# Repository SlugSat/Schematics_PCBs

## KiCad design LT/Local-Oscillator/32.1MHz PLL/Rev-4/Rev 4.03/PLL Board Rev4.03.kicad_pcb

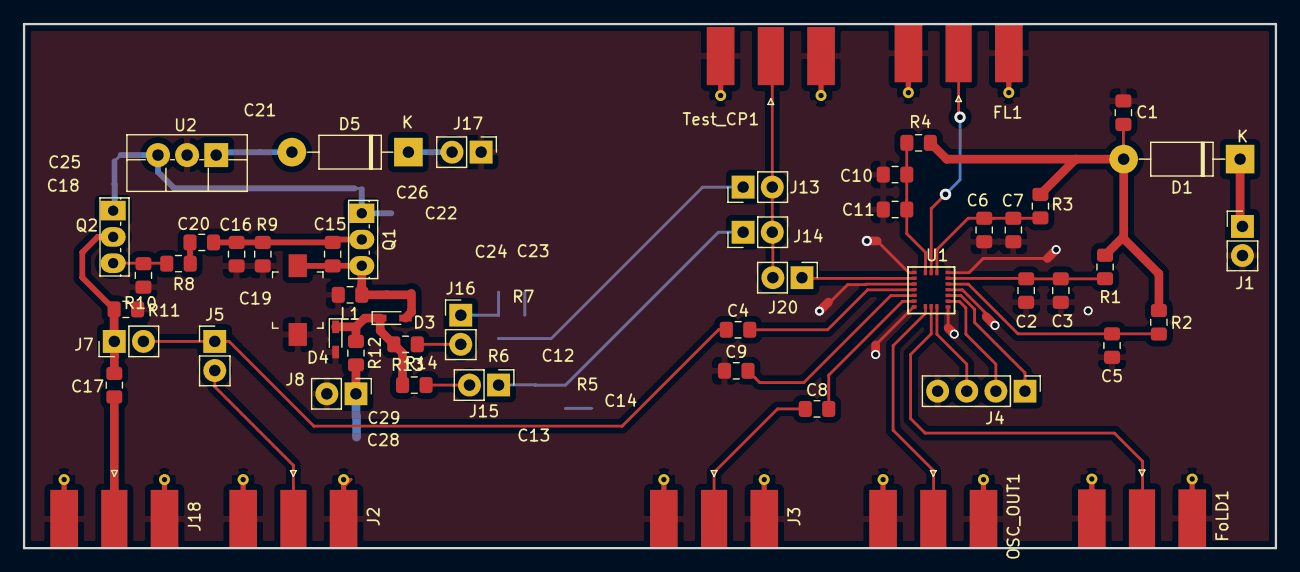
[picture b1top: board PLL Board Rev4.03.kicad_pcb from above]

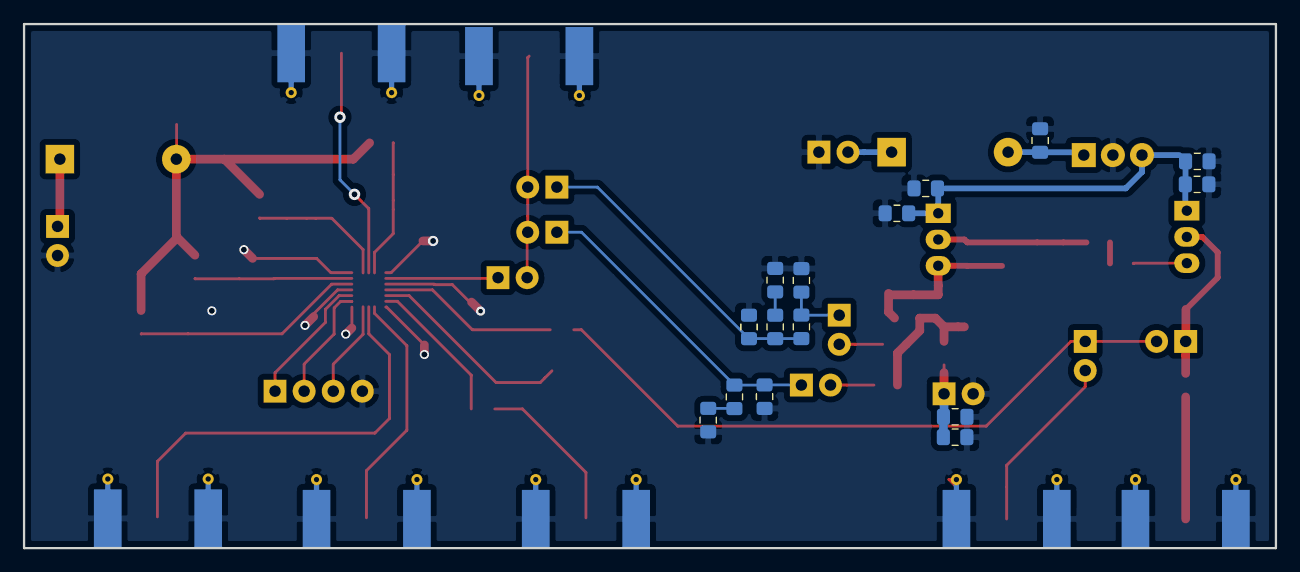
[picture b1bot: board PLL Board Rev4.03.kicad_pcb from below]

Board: 2 copper layers, 109.2 x 45.7 mm, 69 parts (15 on the bottom side), 39 nets.

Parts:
C1, C13, C14: C; C_0805_2012Metric_Pad1.15x1.40mm_HandSolder
C2, C5, C6, C9, C10, C17, C18, C21, C22, C29: 100nF; C_0805_2012Metric_Pad1.15x1.40mm_HandSolder
C3, C7, C11, C25, C26, C28: 100pF; C_0805_2012Metric_Pad1.15x1.40mm_HandSolder
C4, C8: 1000pF; C_0805_2012Metric_Pad1.15x1.40mm_HandSolder
C12: 12nF; C_0805_2012Metric_Pad1.15x1.40mm_HandSolder
C15: 22pF; C_0805_2012Metric_Pad1.15x1.40mm_HandSolder
C16: 47pF; C_0805_2012Metric_Pad1.15x1.40mm_HandSolder
C19: TZB4Z100BA10R00; C_Trimmer_Murata_TZB4-B
C20: 10pF; C_0805_2012Metric_Pad1.15x1.40mm_HandSolder
C23: 80nF; C_0805_2012Metric_Pad1.15x1.40mm_HandSolder
C24: 220nF; C_0805_2012Metric_Pad1.15x1.40mm_HandSolder
D1, D5: DIODE; D_DO-41_SOD81_P10.16mm_Horizontal
D3, D4: ???; D_SC-80_HandSoldering
FL1: Conn_Coaxial; SMA_Molex_73251-1153_EdgeMount_Horizontal
FoLD1: Conn_Coaxial; SMA_Molex_73251-1153_EdgeMount_Horizontal
J1, J5, J7, J8, J13, J14, J15, J16, J17, J20: Conn_01x02_Male; PinHeader_1x02_P2.54mm_Vertical
J2, J3, J18: Conn_Coaxial; SMA_Molex_73251-1153_EdgeMount_Horizontal
J4: Conn_01x04_Male; PinHeader_1x04_P2.54mm_Vertical
L1: 680nH; L_0805_2012Metric_Pad1.15x1.40mm_HandSolder
OSC_OUT1: Conn_Coaxial; SMA_Molex_73251-1153_EdgeMount_Horizontal
Q1, Q2: 2N5486 JFET; TO-251-3_Vertical
R1, R3, R4: 18; R_0805_2012Metric_Pad1.15x1.40mm_HandSolder
R2: 10k; R_0805_2012Metric_Pad1.15x1.40mm_HandSolder
R5: R; R_0805_2012Metric_Pad1.15x1.40mm_HandSolder
R6, R9, R11, R12: 1k; R_0805_2012Metric_Pad1.15x1.40mm_HandSolder
R7: 62k; R_0805_2012Metric_Pad1.15x1.40mm_HandSolder
R8: 1 Ohm; R_0805_2012Metric_Pad1.15x1.40mm_HandSolder
R10: 100k; R_0805_2012Metric_Pad1.15x1.40mm_HandSolder
R13, R14: 0; R_0805_2012Metric_Pad1.15x1.40mm_HandSolder
Test_CP1: Conn_Coaxial; SMA_Molex_73251-1153_EdgeMount_Horizontal
U1: LMX231X
U2: L7808; TO-220F-3_Vertical

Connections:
8V: C18.2, C22.2, C25.2, C26.2, Q1.1, Q2.1, U2.3
CE: C5.2, R2.2, U1.15
CPo: J20.1, U1.2
Clock: J4.3, U1.10
Data: J4.2, U1.12
FL: FL1.1, U1.19
F_IN: C4.2, U1.4
FoLD: FoLD1.1, U1.9
GND: C1.1, C2.1, C3.1, C5.1, C6.1, C7.1, C9.1, C10.1, C11.1, C12.1, C13.2, C14.2, C16.1, C18.1, C19.2, C21.2, C22.1, C23.2, C24.2, C25.1, C26.1, C28.1, C29.1, D4.2, FL1.2, FoLD1.2, J1.2, J2.2, J3.2, J4.4, J8.2, J17.1, J18.2, L1.2, OSC_OUT1.2, R9.2, R10.1, R11.2, Test_CP1.2, U1.1, U1.3, U1.7, U1.11, U1.14, U1.17, U2.2
LE: J4.1, U1.13
unnamed: C4.1, J5.1, J7.2
unnamed: C8.1, J3.1
unnamed: C9.2, U1.5
unnamed: C12.2, J13.1, R6.2, R7.2
unnamed: C13.1, J14.1, J15.1, R5.2
unnamed: C14.1, R5.1
unnamed: C15.1, C16.2, C20.1, Q1.2, R9.1
unnamed: C15.2, C19.1, D3.2, L1.1, Q1.3
unnamed: C17.1, J7.1, Q2.2, R11.1
unnamed: C17.2, J18.1
unnamed: C20.2, R8.2
unnamed: C21.1, D5.2, U2.1
unnamed: C23.1, R7.1
unnamed: C24.1, J16.1, R6.1
unnamed: C28.2, C29.2, J8.1, R12.2
unnamed: D1.1, J1.1
unnamed: D3.1, D4.1, R12.1, R13.2, R14.2
unnamed: D5.1, J17.2
unnamed: J2.1, J5.2
unnamed: J13.2, J14.2, J20.2, Test_CP1.1
unnamed: J15.2, R13.1
unnamed: J16.2, R14.1
unnamed: Q2.3, R8.1, R10.2
OSC_IN: C8.2, U1.6
OSC_OUT: OSC_OUT1.1, U1.8
PLL_Power: C1.2, D1.2, R1.1, R2.1, R3.1, R4.1
V_uC: C2.2, C3.2, R1.2, U1.16
Vcc: C6.2, C7.2, R3.2, U1.18
Vp: C10.2, C11.2, R4.2, U1.20

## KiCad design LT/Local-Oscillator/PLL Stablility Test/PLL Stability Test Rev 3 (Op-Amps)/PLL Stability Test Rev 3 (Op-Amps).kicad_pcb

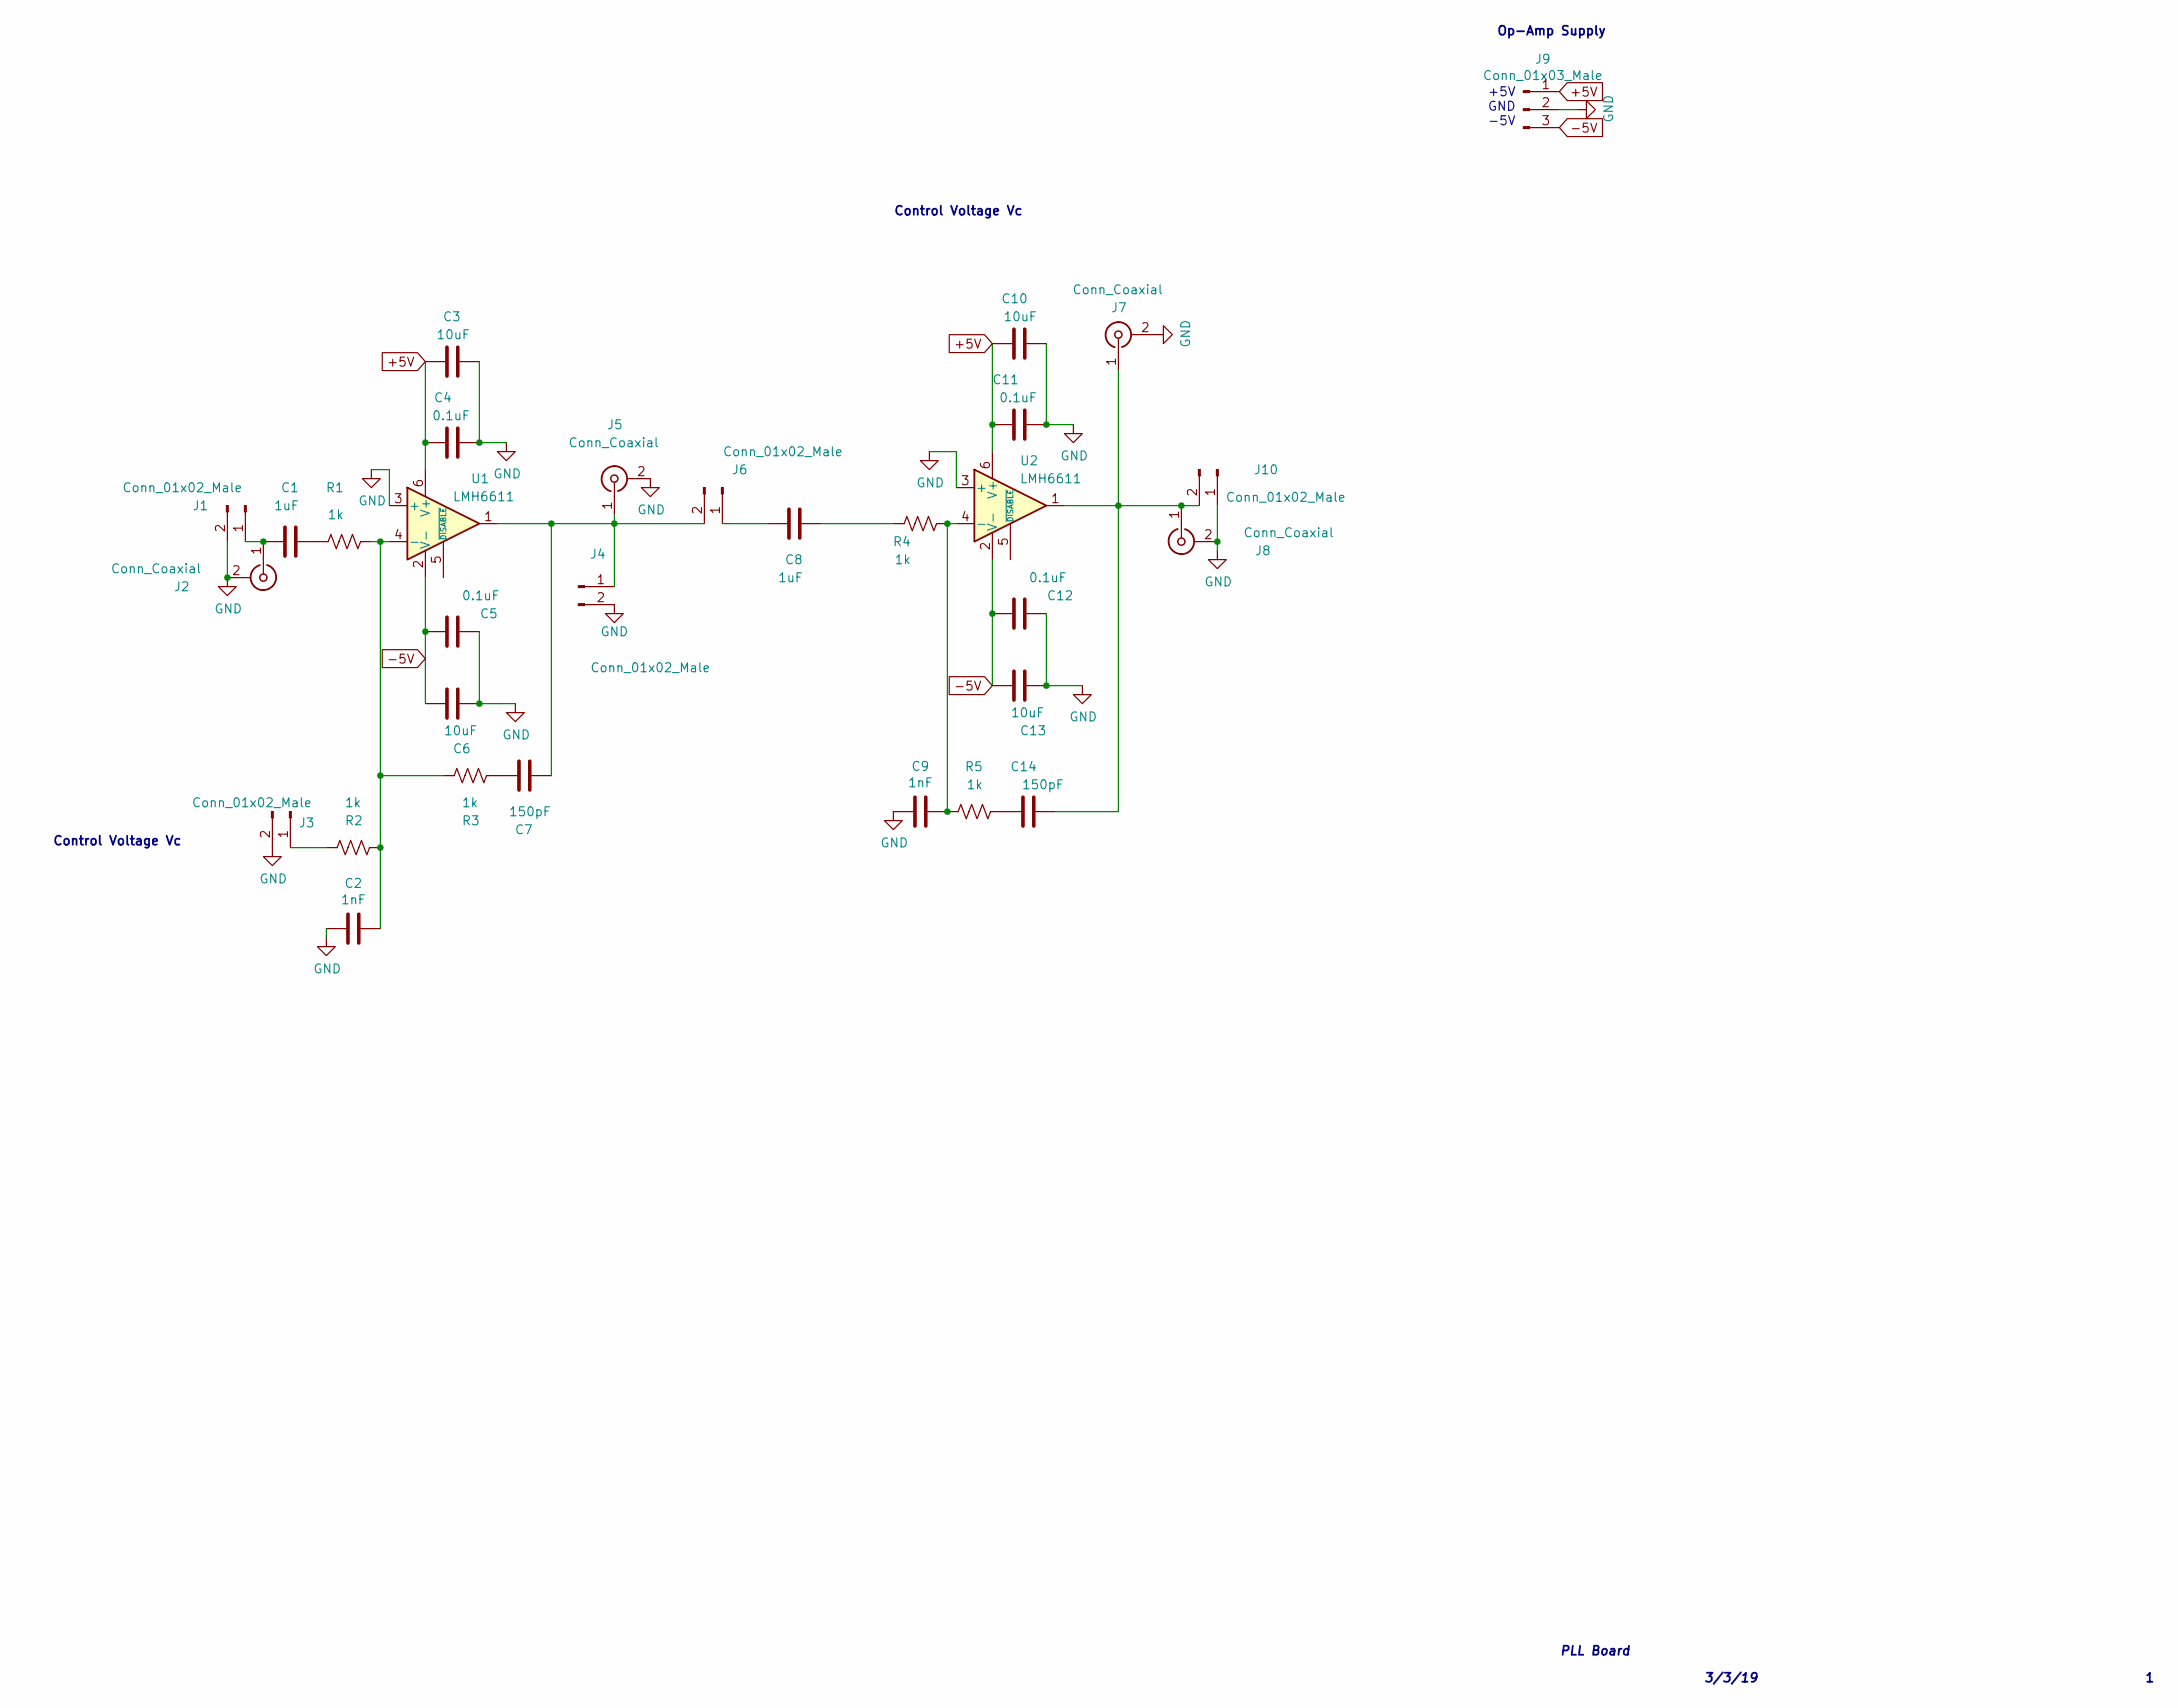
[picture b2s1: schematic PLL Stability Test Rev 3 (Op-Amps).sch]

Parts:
C1, C8: 1uF; C_0805_2012Metric_Pad1.15x1.40mm_HandSolder
C2, C9: 1nF; C_0805_2012Metric_Pad1.15x1.40mm_HandSolder
C3, C6, C10, C13: 10uF; C_0805_2012Metric_Pad1.15x1.40mm_HandSolder
C4, C5, C11, C12: 0.1uF; C_0805_2012Metric_Pad1.15x1.40mm_HandSolder
C7, C14: 150pF; C_0805_2012Metric_Pad1.15x1.40mm_HandSolder
J1, J3, J4, J6, J10: Conn_01x02_Male; PinHeader_1x02_P2.54mm_Vertical
J2, J5, J7, J8: Conn_Coaxial; SMA_Amphenol_132289_EdgeMount
J9: Conn_01x03_Male; PinHeader_1x03_P2.54mm_Vertical
R1, R2, R3, R4, R5: 1k; R_0805_2012Metric_Pad1.15x1.40mm_HandSolder
U1, U2: LMH6611; TSOT-23-6

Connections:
+5V: C3.1, C4.1, C10.1, C11.1, J9.1, U1.6 (V+), U2.6 (V+)
-5V: C5.2, C6.2, C12.2, C13.2, J9.3, U1.2 (V-), U2.2 (V-)
GND: C2.2, C3.2, C4.2, C5.1, C6.1, C9.2, C10.2, C11.2, C12.1, C13.1, J1.2, J2.2 (Ext), J3.2, J4.2, J5.2 (Ext), J7.2 (Ext), J8.2 (Ext), J9.2, J10.1, U1.3 (+), U2.3 (+)
unnamed: C1.1, J1.1, J2.1 (In)
unnamed: C1.2, R1.1
unnamed: C2.1, R1.2, R2.1, R3.2, U1.4 (-)
unnamed: C7.1, R3.1
unnamed: C7.2, J4.1, J5.1 (In), J6.2, U1.1
unnamed: C8.1, J6.1
unnamed: C8.2, R4.1
unnamed: C9.1, R4.2, R5.2, U2.4 (-)
unnamed: C14.1, R5.1
unnamed: C14.2, J7.1 (In), J8.1 (In), J10.2, U2.1
unnamed: J3.1, R2.2

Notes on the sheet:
PLL Board
3/3/19
+5V GND -5V
Op-Amp Supply
Control Voltage Vc

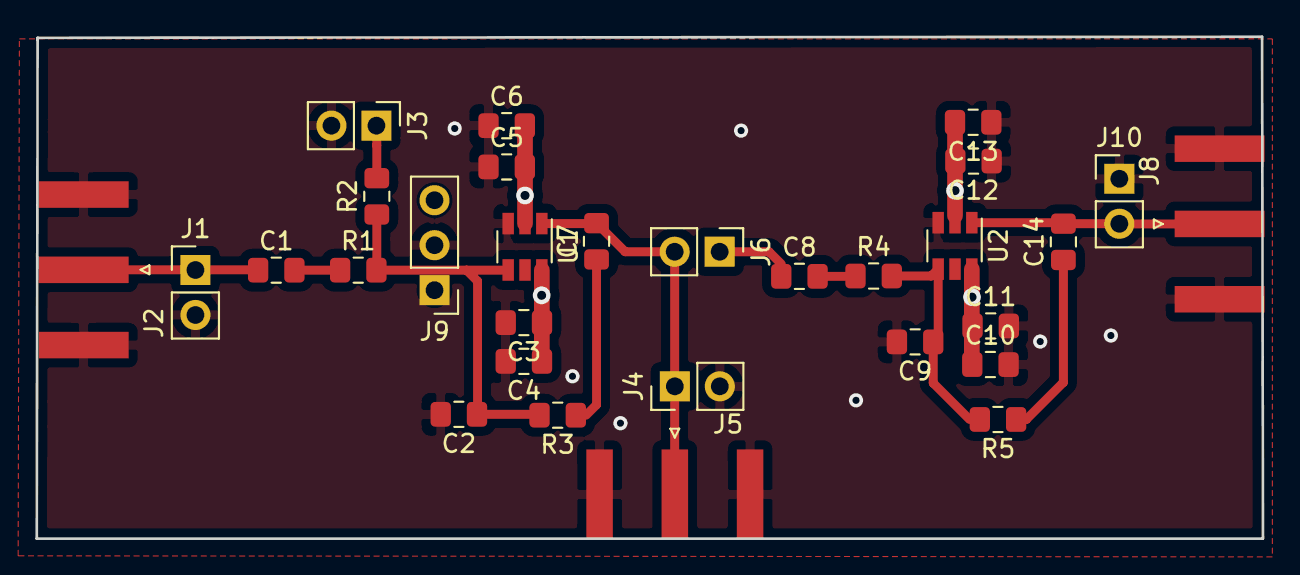
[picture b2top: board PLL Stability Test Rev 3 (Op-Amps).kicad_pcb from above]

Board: 2 copper layers, 69.2 x 28.3 mm, 30 parts (0 on the bottom side), 14 nets.

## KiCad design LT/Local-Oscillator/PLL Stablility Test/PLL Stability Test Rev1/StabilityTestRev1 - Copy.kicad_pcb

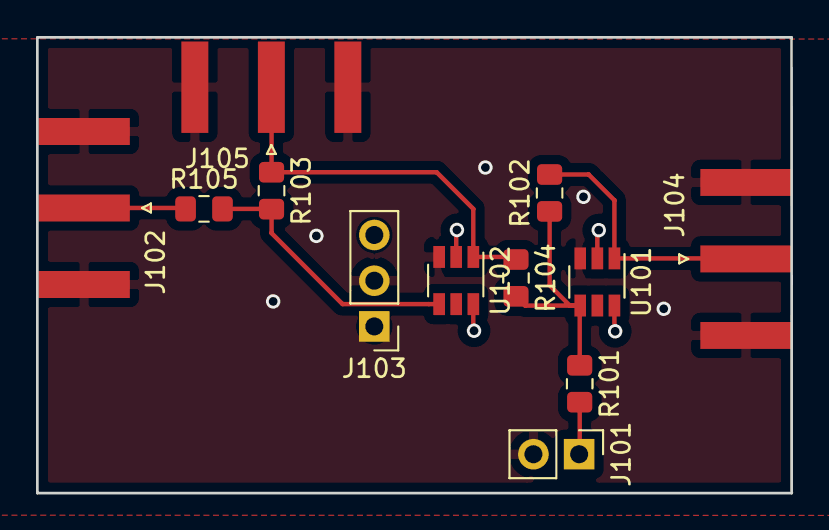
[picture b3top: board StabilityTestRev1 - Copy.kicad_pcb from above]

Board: 2 copper layers, 41.9 x 25.3 mm, 12 parts (0 on the bottom side), 9 nets.

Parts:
J101: Conn_01x02_Male; PinHeader_1x02_P2.54mm_Vertical
J102, J104, J105: Conn_Coaxial; SMA_Amphenol_132289_EdgeMount
J103: Conn_01x03_Male; PinHeader_1x03_P2.54mm_Vertical
R101, R102, R103, R104, R105: 1k; R_0805_2012Metric_Pad1.15x1.40mm_HandSolder
U101, U102: LMH6611; TSOT-23-6

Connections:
+5V: J103.1, U101.6, U102.6
-5V: J103.3, U101.2, U102.2
GND: J101.2, J102.2, J103.2, J104.2, J105.2, U101.3, U102.3
unnamed: J101.1, R101.2
unnamed: J102.1, R105.1
unnamed: J104.1, R102.2, U101.1
unnamed: J105.1, R103.1, R104.1, U102.1
unnamed: R101.1, R102.1, R104.2, U101.4
unnamed: R103.2, R105.2, U102.4
